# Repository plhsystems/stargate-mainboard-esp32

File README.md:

# Stargate Mainboard ESP32

A fully functional Stargate replica controller based on ESP32, designed to replace Raspberry Pi-based solutions with a more cost-effective and integrated approach.

## Overview

This project provides a complete embedded system for controlling Stargate props designed by Kristian and the "Build The Stargate" community. The ESP32-based solution offers:

- **Lower Cost**: ESP32 modules are significantly cheaper than Raspberry Pi
- **Better Availability**: No shortage issues
- **Integrated Design**: All drivers, regulators, and control circuitry on a single PCB
- **Simpler Wiring**: Fewer external breakouts required
- **Real-Time Control**: FreeRTOS-based deterministic motor control

## Features

### ✅ Implemented

#### Core Functionality
- ✅ **Web Interface**: Full-featured HTTP server with REST API
- ✅ **WiFi**: Station + SoftAP dual-mode support
- ✅ **OTA Updates**: Over-the-air firmware updates
- ✅ **Configuration Management**: JSON import/export
- ✅ **Multiple Gate Types**: Movie/SG1, Atlantis, Universe support

#### Hardware Control
- ✅ **Ring Motor Control**: Stepper motor with precise positioning
- ✅ **Chevron Control**: 9 chevron LED lighting (configurable for 7)
- ✅ **Servo Control**: Chevron locking mechanism (MCPWM-based)
- ✅ **Wormhole LEDs**: 48 NeoPixel LED effects
- ✅ **Ramp Lighting**: PWM-controlled LED brightness
- ✅ **Audio System**: Integrated amplifier with sound effects

#### Advanced Features
- ✅ **Auto-Homing**: Hall sensor-based ring calibration
- ✅ **Auto-Calibration**: Automatic steps-per-rotation detection
- ✅ **BLE Communication**: Wireless control of smart ring LEDs
- ✅ **Address Book**: Hardcoded and fan gate addresses
- ✅ **Incoming Wormholes**: Support for remote gate dialing
- ✅ **Diagnostic Mode**: Hardware testing and troubleshooting

### 🚧 In Progress

- 🚧 **DHD Board Support**: Integration with STM32-based DHD
- 🚧 **SD Card Support**: External storage for audio assets

**Note**: Pablo Board HAL is not yet ready to work and should not be used.

### 📋 Planned

- 📋 **Subspace Network**: Connection to other fan gates
- 📋 **Mobile App**: Dedicated iOS/Android control
- 📋 **Voice Control**: Smart home integration
- 📋 **Advanced Wormhole Effects**: Blackhole, unstable wormhole

## Quick Start

### Prerequisites

- **Hardware**: ESP32-S3 mainboard (pinky-board or compatible)
- **Software**: ESP-IDF 5.3.1
- **Tools**: Python 3.8+, CMake, Ninja

### Installation

1. **Install ESP-IDF 5.3**:
```bash
mkdir -p ~/esp
cd ~/esp
git clone -b v5.3.1 --recursive https://github.com/espressif/esp-idf.git esp-idf-5.3
cd esp-idf-5.3
./install.sh
```

2. **Clone Repository**:
```bash
git clone https://github.com/user/stargate-mainboard-esp32.git
cd stargate-mainboard-esp32
```

3. **Build and Flash**:
```bash
cd firmware/stargate-fw/pinky-board
. ~/esp/esp-idf-5.3/export.sh
idf.py build
idf.py -p /dev/ttyUSB0 flash monitor
```

### First-Time Setup

1. Power on the ESP32
2. Connect to WiFi network `Stargate-Universe`
3. Navigate to `http://192.168.4.1`
4. Follow the setup wizard
5. Configure WiFi and gate type
6. Run homing sequence

## Architecture

The system consists of multiple firmware components:

- **stargate-fw**: Main controller (ESP32-S3)
  - Gate control state machine
  - Web server and REST API
  - WiFi and BLE management
  - Motor control and sensor reading

- **ring-fw**: Smart ring controller (ESP32)
  - BLE server for receiving commands
  - 48 NeoPixel LED control
  - Animation effects and power management

- **ring-factory**: Factory test firmware
  - Hardware diagnostics
  - Burn-in testing
  - Factory reset capability

For detailed architecture information, see [doc/architecture.md](doc/architecture.md).

## Documentation

Comprehensive documentation is available in the [doc/](doc/) directory:

### Essential Reading
- [📖 Architecture](doc/architecture.md) - System design and components
- [🔌 BLE Protocol](doc/ble-protocol.md) - Ring communication details
- [🌐 API Reference](doc/api-reference.md) - HTTP REST API
- [🏠 Homing Algorithm](doc/homing-algorithm.md) - Ring calibration
- [📞 Dial Algorithm](doc/dial-algorithm.md) - Symbol positioning math

### User Guides
- [🎮 Control Page](doc/control-page.md) - Operating the gate
- [⚙️ Configuration](doc/configuration-page.md) - Settings management
- [🔧 Diagnostic Page](doc/diagnostic-page.md) - Troubleshooting
- [📦 OTA Updates](doc/ota-page.md) - Firmware updates

### Technical Details
- [🌌 Stargate Types](doc/stargate-types.md) - Gate specifications
- [🌀 Wormhole Types](doc/wornhole-types.md) - Visual effects
- [📥 Incoming Wormhole](doc/incoming-wormhole.md) - Receiving dials
- [💾 Partitions](doc/partitions.md) - Flash memory layout

## Hardware

### Pinky Board (Production)

**Specifications**:
- MCU: ESP32-S3-WROOM-1
- Flash: 16 MB
- PSRAM: 8 MB
- WiFi: 802.11 b/g/n
- Bluetooth: BLE 5.0

**Connections**:
```
Stepper Motor:  GPIO 25 (Step), GPIO 33 (Dir), GPIO 26 (Sleep)
Servo Motor:    GPIO 4 (MCPWM)
Hall Sensor:    GPIO 32 (Input)
Wormhole LEDs:  GPIO 27 (WS2812B - 48 LEDs)
Ramp LED:       GPIO 23 (PWM)
Status LED:     GPIO 5
```

### Ring Board

**Specifications**:
- MCU: ESP32-WROOM-32
- Flash: 4 MB
- BLE: Server mode

**Connections**:
```
NeoPixel Ring:  GPIO 13 (48 LEDs in 4 concentric rings)
```

## API Examples

### Dial an Address
```bash
curl -X POST http://stargate.local/api/gate/dial \
  -H "Content-Type: application/json" \
  -d '{
    "address": [27, 7, 15, 32, 12, 30, 1],
    "galaxy": "milky_way"
  }'
```

### Get Status
```bash
curl http://stargate.local/api/system/status
```

### Control Ring LEDs
```bash
curl -X POST http://stargate.local/api/ring/animation \
  -H "Content-Type: application/json" \
  -d '{"animation": "fade_in"}'
```

For complete API documentation, see [doc/api-reference.md](doc/api-reference.md).

## Development

### Project Structure
```
stargate-mainboard-esp32/
├── firmware/
│   ├── stargate-fw/        # Main controller
│   │   ├── main-app/       # Application logic
│   │   └── pinky-board/    # Hardware implementation
│   ├── ring-fw/            # Ring controller
│   └── ring-factory/       # Factory test firmware
├── esp32-components/       # Shared utilities
│   └── misc-formula/       # Math functions
├── sgc-components/         # Stargate-specific
│   └── sgu-ringcomm/       # BLE protocol
└── doc/                    # Documentation
```

### Building Different Targets

**Main Controller**:
```bash
cd firmware/stargate-fw/pinky-board
idf.py build
```

**Ring Firmware**:
```bash
cd firmware/ring-fw
idf.py build
```

**Factory Test**:
```bash
cd firmware/ring-factory
idf.py build
```

### Code Style

- C++ Standard: C++17
- Naming: PascalCase for classes, camelCase for methods
- Indentation: 4 spaces
- Comments: Doxygen format for APIs

## Why ESP32 over Raspberry Pi?

| Feature | ESP32 | Raspberry Pi |
|---------|-------|--------------|
| Cost | ~$5-10 | ~$35-75 |
| Availability | Readily available | Frequent shortages |
| Real-time Control | Yes (FreeRTOS) | Limited (Linux) |
| Power Consumption | ~80mA | ~500mA+ |
| Boot Time | <1 second | 20-40 seconds |
| Integration | Single PCB possible | Requires breakouts |
| GPIO | 34 pins | 28 pins (40-pin header) |
| Reliability | No SD card corruption | SD card wear issues |

## Troubleshooting

### Build Issues

**MCPWM API errors**:
- Ensure ESP-IDF 5.3+ is installed
- Check compatibility notes in [doc/architecture.md](doc/architecture.md)

**BLE compilation errors**:
- Add required NimBLE headers
- Include `#undef min` / `#undef max` after includes

**IRAM overflow**:
- Set `CONFIG_COMPILER_OPTIMIZATION_SIZE=y` in sdkconfig

### Runtime Issues

**Ring won't connect**:
- Verify ring is powered
- Check BLE is enabled
- Check logs: `idf.py monitor`

**Stepper doesn't move**:
- Check sleep pin (GPIO 26) is HIGH
- Verify power supply to stepper driver
- Test with manual step command

**Homing fails**:
- Check hall sensor wiring (GPIO 32)
- Run manual homing via web interface
- Verify sensor triggers when magnet is near

## Contributing

Contributions are welcome! Please:

1. Read the documentation in [doc/](doc/)
2. Follow the code style guidelines
3. Test thoroughly on hardware
4. Submit pull requests with clear descriptions

## Community

- **Forum**: [Build The Stargate Community](https://buildthestargateproject.com/)
- **Discord**: [Stargate Builders](https://discord.gg/stargate)
- **YouTube**: [Kristian's Channel](https://youtube.com/kristian)

## License

See [doc/copyright.md](doc/copyright.md) for licensing information.

## Acknowledgments

- **Kristian**: Original Stargate design and inspiration
- **Build The Stargate Project**: Community support
- **Espressif**: ESP-IDF framework
- **Contributors**: Everyone who helped make this possible

---

**Current Version**: 1.0.0
**ESP-IDF Version**: 5.3.1
**Last Updated**: 2026-01-22

For detailed documentation, visit the [doc/](doc/) directory.

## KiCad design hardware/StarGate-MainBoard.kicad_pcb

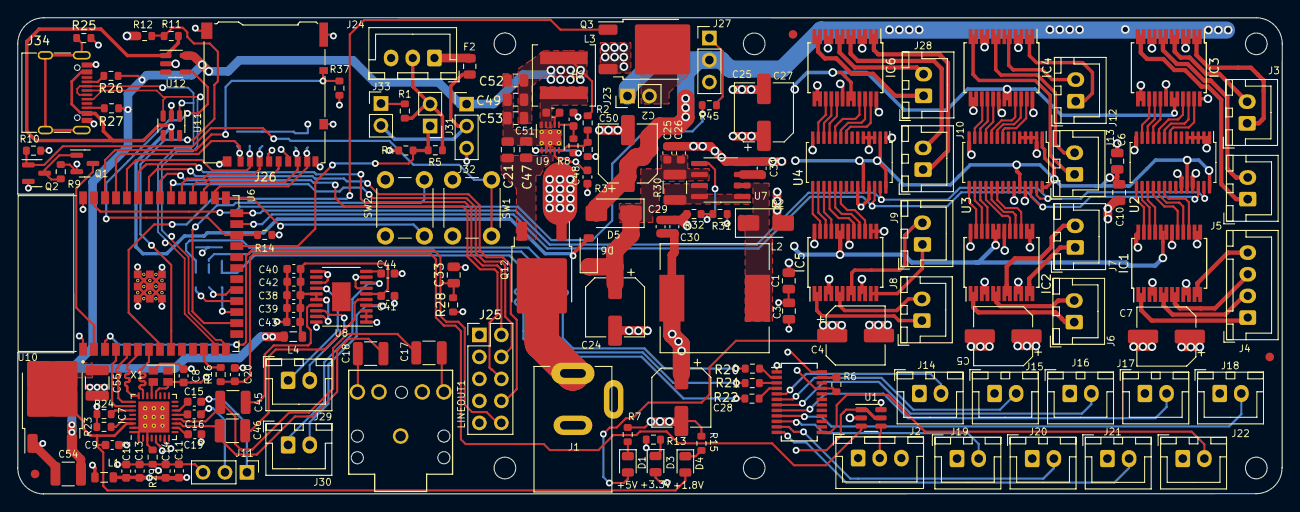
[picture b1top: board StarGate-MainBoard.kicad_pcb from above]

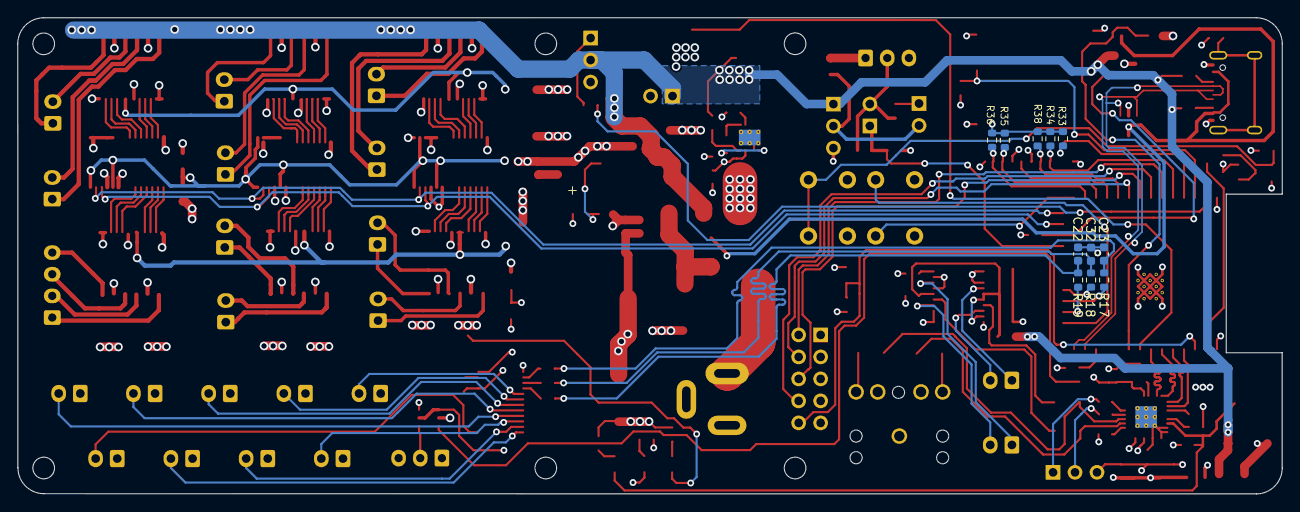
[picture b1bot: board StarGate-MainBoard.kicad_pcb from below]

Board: 4 copper layers, 146.1 x 55.0 mm, 171 parts (11 on the bottom side), 163 nets.

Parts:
C1, C3, C33: 0.1uF; C_0805_2012Metric
C2, C4, C5, C7: 47uF/16V; CP_Elec_6.3x7.7
C6, C10: 10uF; C_0805_2012Metric
C8, C9, C11, C13, C19, C25, C29, C38, C40, C44: 100nF; C_0603_1608Metric
C12, C20, C22, C23, C26, C30, C32, C39, C41: 10nF; C_0603_1608Metric
C14: 4u7F; C_0603_1608Metric
C15, C16, C42, C43: 1uF; C_0603_1608Metric
C17, C18, C45, C46: 100uF 10V; C_1210_3225Metric
C21, C47: 10uF 25V; C_0805_2012Metric
C24: 100uF; CP_Elec_6.3x7.7
C27, C28: 220uF; CP_Elec_6.3x7.7
C31: 120pF; C_0603_1608Metric
C48, C50: 0.1uF; C_0603_1608Metric
C49, C52, C53: 22uF 25V; C_0805_2012Metric
C51: 0.1uF 50V; C_0603_1608Metric
C54: 10uF; C_1210_3225Metric
C55: 22uF; C_1210_3225Metric
D1, D3, D4: LED; LED_0805_2012Metric
D2: STPS2150A; D_SMA
D5: D; D_SMA
D6: D; D_SOD-123
F2: Polyfuse; Fuse_0805_2012Metric
FID1, FID2, FID3: FIDUCIAL""; Fiducial_1mm_Mask2mm
H1, H2, H3, H4, H5, H6: MountingHole; MountingHole_2.5mm
IC1, IC2, IC3, IC4, IC5, IC6: TB6612FNG; SSOP-24_5.3x8.2mm_P0.65mm
IC7: SGTL5000; QFN-32-1EP_5x5mm_P0.5mm_EP3.6x3.6mm_ThermalVias
J1: PJ-037A; CUI_PJ-037A
J2, J24: Conn_01x03_Socket; JST_XH_B3B-XH-A_1x03_P2.50mm_Vertical
J3, J5, J6, J7, J8, J9, J10, J12, J13, J14, J15, J16, J17, J18, J19, J20, J21, J22, J28, J29, J30: Conn_01x02_Pin; JST_XH_B2B-XH-A_1x02_P2.50mm_Vertical
J4: Conn_01x04_Pin; JST_XH_B4B-XH-A_1x04_P2.50mm_Vertical
J11, J27, J32: Conn_01x03_Male; PinHeader_1x03_P2.54mm_Vertical
J23, J31, J33: Conn_01x02_Pin; PinHeader_1x02_P2.54mm_Vertical
J25: Conn_02x05_Odd_Even; PinHeader_2x05_P2.54mm_Vertical
J26: Micro_SD_Card_Det; microSD_HC_Hirose_DM3AT-SF-PEJM5
J34: USB_C_Receptacle; USB_C_Receptacle_G-Switch_GT-USB-7010ASV
L1, L4: 15uH; L_0805_2012Metric
L2: 220uH; L_12x12mm_H4.5mm
L3: 2.2uH 6x6; L_Coilcraft_XAL6060-XXX
LINEOUT1: Phonejack_Stereo_SW; StereoJack_3.5mm_Switch_Cliff_JY039-5P_Horizontal
Q1: FDN340P; SOT-23
Q2: FDN337N; SOT-23
Q3: N0400P-ZK-E1-AY; TO-252-3_TabPin2
Q12: PMOS; TO-252-3_TabPin2
R1, R5: 6.8k; R_0603_1608Metric
R2, R14, R33, R34, R35, R36, R37, R38: 22k; R_0603_1608Metric
R3: 3k; R_0603_1608Metric
R4: 13k; R_0603_1608Metric
R6: R; R_0603_1608Metric
R7, R13, R15: 1K; R_0603_1608Metric
R8: 100k; R_0603_1608Metric
R9, R10, R16, R17, R18, R19, R28: 10k; R_0603_1608Metric
R11: 348k; R_0603_1608Metric
R12: 649k; R_0603_1608Metric
R20, R21, R22: 120R; R_0603_1608Metric
R23, R24: 2k2; R_0603_1608Metric
R25: 1M; R_0603_1608Metric
R26, R27: 5.1k; R_0603_1608Metric
R29: 0R; R_0603_1608Metric
R30: 0R33; R_1210_3225Metric
R31: 6k2; R_0603_1608Metric
R32: 3k9; R_0603_1608Metric
R45: 1k; R_0603_1608Metric
SW1, SW2: SW_Push_Dual; SW_PUSH_6mm
U1: SN74LVC1T45DBV; SOT-23-6
U2, U3, U4: PCA9685; TSSOP-28_4.4x9.7mm_P0.65mm
U5: FM6124; SSOP-24_3.9x8.7mm_P0.635mm
U6: ESP32-S3-WROOM-1-N16R2; XCVR_ESP32-S3-WROOM-1-N16R2
U7: MC33063ADR; SOIC-8_3.9x4.9mm_P1.27mm
U8: TPA6017A2; TSSOP-20-1EP_4.4x6.5mm_P0.65mm_EP2.15x3.35mm
U9: RT6219; WDFN-10-1EP_3x3mm_P0.5mm_EP1.8x2.5mm_ThermalVias
U10: AZ1084-1.8; TO-252-2
U11: USBLC6-4SC6; SOT-23-6
U12: STMPS2151STR; SOT-23-5
X1: SG-210SDF (11.2896MHz); Oscillator_SMD_SeikoEpson_SG210-4Pin_2.5x2.0mm

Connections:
+1V8: C9.1, C55.2, D4.2 (A), IC7.30 (VDDD), U10.2 (VO)
+3.3VA: C11.1, C12.2, C13.2, C14.2, IC7.5 (VDDA), L1.2
+3V3: C1.1, C3.1, C6.1, C8.1, C10.1, C27.1, C28.1, C29.1, C30.1, C48.2, D3.2 (A), IC1.19 (STBY), IC1.20 (VCC), IC2.19 (STBY), IC2.20 (VCC), IC3.19 (STBY), IC3.20 (VCC), IC4.19 (STBY), IC4.20 (VCC), IC5.19 (STBY), IC5.20 (VCC), IC6.19 (STBY), IC6.20 (VCC), IC7.20 (VDDIO), J25.1, J26.4 (VDD), J32.3, L1.1, L2.1, Q1.2 (S), R9.1, R10.1, R23.1, R24.1, R28.1, R31.1, R33.1, R34.1, R35.1, R36.1, R37.1, R38.1, U1.1 (VCCA), U1.5 (DIR), U2.24 (A5), U2.28 (VDD), U3.1 (A0), U3.24 (A5), U3.28 (VDD), U4.2 (A1), U4.24 (A5), U4.28 (VDD), U5.24 (VDD), U9.4 (EN), X1.4 (Vcc)
+5V: C2.1, C4.1, C5.1, C7.1, C49.2, C52.2, C53.2, C54.2, D1.2 (A), D5.2 (A), IC1.13 (VM2), IC1.14 (VM3), IC1.24 (VM1), IC2.13 (VM2), IC2.14 (VM3), IC2.24 (VM1), IC3.13 (VM2), IC3.14 (VM3), IC3.24 (VM1), IC4.13 (VM2), IC4.14 (VM3), IC4.24 (VM1), IC5.13 (VM2), IC5.14 (VM3), IC5.24 (VM1), IC6.13 (VM2), IC6.14 (VM3), IC6.24 (VM1), J2.1, J14.1, J15.1, J16.1, J17.1, J18.1, J19.1, J20.1, J21.1, J22.1, J23.1, J27.2, J32.1, L3.2, L4.2, R2.1, R26.1, R27.1, U1.6 (VCCB), U10.3 (VI), U12.5 (IN)
+12V: C21.2, C47.2, Q12.3 (S), U9.3 (VIN)
/AMP_VDD: C38.1, C39.1, C40.1, C41.1, C42.1, C43.1, L4.1, U8.6 (PVDD), U8.15 (PVDD), U8.16 (VDD), U8.19 (SHUTDOWN)
/BOOT_MODE_A: SW2.2, U6.27 (IO0)
/BOOT_MODE_B: SW2.4, U6.16 (IO46)
/D_N: J34.A7 (D-), J34.B7 (D-), U6.13 (IO19), U11.1 (I/O1)
/D_P: J34.A6 (D+), J34.B6 (D+), U6.14 (IO20), U11.3 (I/O2)
/I2C_SCL_B: IC7.29 (CTRL_CLK), R23.2
/I2C_SDA_B: IC7.27 (CTRL_DATA), R24.2
/I2S_DIN: IC7.26 (I2S_DIN), U6.4 (IO4)
/I2S_DOUT: IC7.25 (I2S_DOUT), U6.5 (IO5)
/I2S_LRCLK: IC7.23 (I2S_LRCLK), U6.7 (IO7)
/I2S_SCLK: IC7.24 (I2S_SCLK), U6.6 (IO6)
/LED1: J14.2, U5.5 (OUT0)
/LED2: J15.2, U5.6 (OUT1)
/LED3: J16.2, U5.7 (OUT2)
/LED4: J17.2, U5.8 (OUT3)
/LED5: J18.2, U5.9 (OUT4)
/LED6: J19.2, U5.10 (OUT5)
/LED7: J20.2, U5.11 (OUT6)
/LED8: J21.2, U5.12 (OUT7)
/LED9: J22.2, U5.13 (OUT8)
/LED_CLK: C32.1, R18.1, R21.1
/LED_LE: C22.1, R19.1, R22.1
/LED_MOSI: C23.1, R17.1, R20.1
/LED_PWM: Q3.2 (G), U6.8 (IO15)
/MTCK: J25.4, U6.32 (IO39)
/MTDI: J25.8, U6.34 (IO41)
/MTDO: J25.6, U6.33 (IO40)
/MTMS: J25.2, U6.35 (IO42)
/NEO_MOSI: C20.1, R16.1, U1.3 (A)
/PROX_IP: J31.1, R4.1, R5.2, U6.23 (IO21)
/PWM1_2: IC3.23 (PWMA), U2.8 (PWM2)
/PWM1_3: IC3.22 (AIN2), U2.9 (PWM3)
/PWM1_4: IC3.21 (AIN1), U2.10 (PWM4)
/PWM1_5: IC3.17 (BIN1), U2.11 (PWM5)
/PWM1_6: IC3.16 (BIN2), U2.12 (PWM6)
/PWM1_7: IC3.15 (PWMB), U2.13 (PWM7)
/PWM1_8: IC1.23 (PWMA), U2.15 (PWM8)
/PWM1_9: IC1.22 (AIN2), U2.16 (PWM9)
/PWM1_10: IC1.21 (AIN1), U2.17 (PWM10)
/PWM1_11: IC1.17 (BIN1), U2.18 (PWM11)
/PWM1_12: IC1.16 (BIN2), U2.19 (PWM12)
/PWM1_13: IC1.15 (PWMB), U2.20 (PWM13)
/PWM2_2: IC4.23 (PWMA), U3.8 (PWM2)
/PWM2_3: IC4.22 (AIN2), U3.9 (PWM3)
/PWM2_4: IC4.21 (AIN1), U3.10 (PWM4)
/PWM2_5: IC4.17 (BIN1), U3.11 (PWM5)
/PWM2_6: IC4.16 (BIN2), U3.12 (PWM6)
/PWM2_7: IC4.15 (PWMB), U3.13 (PWM7)
/PWM2_8: IC2.23 (PWMA), U3.15 (PWM8)
/PWM2_9: IC2.22 (AIN2), U3.16 (PWM9)
/PWM2_10: IC2.21 (AIN1), U3.17 (PWM10)
/PWM2_11: IC2.17 (BIN1), U3.18 (PWM11)
/PWM2_12: IC2.16 (BIN2), U3.19 (PWM12)
/PWM2_13: IC2.15 (PWMB), U3.20 (PWM13)
/PWM3_2: IC6.23 (PWMA), U4.8 (PWM2)
/PWM3_3: IC6.22 (AIN2), U4.9 (PWM3)
/PWM3_4: IC6.21 (AIN1), U4.10 (PWM4)
/PWM3_5: IC6.17 (BIN1), U4.11 (PWM5)
/PWM3_6: IC6.16 (BIN2), U4.12 (PWM6)
/PWM3_7: IC6.15 (PWMB), U4.13 (PWM7)
/PWM3_8: IC5.23 (PWMA), U4.15 (PWM8)
/PWM3_9: IC5.22 (AIN2), U4.16 (PWM9)
/PWM3_10: IC5.21 (AIN1), U4.17 (PWM10)
/PWM3_11: IC5.17 (BIN1), U4.18 (PWM11)
/PWM3_12: IC5.16 (BIN2), U4.19 (PWM12)
/PWM3_13: IC5.15 (PWMB), U4.20 (PWM13)
/SCL: U2.26 (SCL), U3.26 (SCL), U4.26 (SCL), U6.25 (IO48)
/SDA: U2.27 (SDA), U3.27 (SDA), U4.27 (SDA), U6.26 (IO45)
/SD_CK: J26.5 (CLK), U6.30 (IO37)
/SD_CMD: J26.3 (CMD), R38.2, U6.31 (IO38)
/SD_D0: J26.7 (DAT0), R35.2, U6.29 (IO36)
/SD_D1: J26.8 (DAT1), R36.2, U6.28 (IO35)
/SD_D2: J26.1 (DAT2), R33.2, U6.37 (TXD0)
/SD_D3: J26.2 (DAT3/CD), R34.2, U6.36 (RXD0)
/SD_DETECT: J26.10 (DET_A), R37.2, U6.38 (IO2)
/SERVO: R45.1, U6.39 (IO1)
/USB_VBUS_DET: R11.2, R12.1, U6.9 (IO16)
/USB_VBUS_EN: R14.1, U6.24 (IO47), U12.4 (EN)
/VBUS: D6.2 (A), J34.A4 (VBUS), J34.A9 (VBUS), J34.B4 (VBUS), J34.B9 (VBUS), R11.1, U11.5 (VBUS), U12.1 (OUT)
/nRESET: C33.1, J25.10, R28.2, U6.3 (EN)
GND: C1.2, C2.2, C3.2, C4.2, C5.2, C6.2, C7.2, C8.2, C9.2, C10.2, C20.2, C21.1, C22.2, C23.2, C24.2, C25.2, C26.2, C27.2, C28.2, C29.2, C30.2, C31.2, C32.2, C33.2, C47.1, C48.1, C49.1, C50.2, C52.1, C53.1, C54.1, C55.1, D2.2 (A), IC1.3 (PGND1), IC1.4 (PGND1'), IC1.9 (PGND2), IC1.10 (PGND2'), IC1.18 (GND), IC2.3 (PGND1), IC2.4 (PGND1'), IC2.9 (PGND2), IC2.10 (PGND2'), IC2.18 (GND), IC3.3 (PGND1), IC3.4 (PGND1'), IC3.9 (PGND2), IC3.10 (PGND2'), IC3.18 (GND), IC4.3 (PGND1), IC4.4 (PGND1'), IC4.9 (PGND2), IC4.10 (PGND2'), IC4.18 (GND), IC5.3 (PGND1), IC5.4 (PGND1'), IC5.9 (PGND2), IC5.10 (PGND2'), IC5.18 (GND), IC6.3 (PGND1), IC6.4 (PGND1'), IC6.9 (PGND2), IC6.10 (PGND2'), IC6.18 (GND), IC7.1 (GND), IC7.3 (GND), IC7.31 (CTRL_ADR0_CS), IC7.32 (CTRL_MODE), IC7.33 (GND), J1.-\ (2), J2.3, J24.3, J25.3, J25.5, J25.9, J26.6 (VSS), J26.9 (DET_B), J26.11 (SHIELD), J27.3, J34.A1 (GND), J34.A12 (GND), J34.B1 (GND), J34.B12 (GND), Q2.2 (S), Q3.3 (S), Q12.2 (G), R3.2, R4.2, R6.2, R7.1, R12.2, R13.1, R14.2, R15.1, R25.2, R29.2, R32.2, SW1.1, SW1.3, SW2.1, SW2.3, U1.2 (GND), U2.1 (A0), U2.2 (A1), U2.3 (A2), U2.4 (A3), U2.5 (A4), U2.14 (GND), U2.23 (#OE), U2.25 (EXTCLK), U3.2 (A1), U3.3 (A2), U3.4 (A3), U3.5 (A4), U3.14 (GND), U3.23 (#OE), U3.25 (EXTCLK), U4.1 (A0), U4.3 (A2), U4.4 (A3), U4.5 (A4), U4.14 (GND), U4.23 (#OE), U4.25 (EXTCLK), U5.1 (GND), U5.21 (OE), U6.1 (GND), U6.40 (GND), U6.41_1 (GND), U6.41_2 (GND), U6.41_3 (GND), U6.41_4 (GND), U6.41_5 (GND), U6.41_6 (GND), U6.41_7 (GND), U6.41_8 (GND), U6.41_9 (GND), U7.4 (GND), U9.2 (VBYP), U9.11 (PGND), U10.1 (GND), U11.2 (GND), U12.2 (GND), X1.2 (GND)
GNDA: C11.2, C12.1, C13.1, C14.1, C19.2, C38.2, C39.2, C40.2, C41.2, C42.2, C43.2, C44.2, IC7.7 (AGND), J11.3, LINEOUT1.1, R29.1, U8.1 (GND), U8.2 (GAIN0), U8.3 (GAIN1), U8.7 (RIN+), U8.9 (LIN+), U8.11 (GND), U8.13 (GND), U8.20 (GND)
unnamed: C17.2, LINEOUT1.2
unnamed: C18.2, LINEOUT1.4
unnamed: C51.1, L3.1, U9.8 (SW), U9.9 (SW), U9.10 (SW)
unnamed: D1.1 (K), R7.2
unnamed: D2.1 (K), L2.2, U7.2 (SwE)
unnamed: D3.1 (K), R13.2
unnamed: D4.1 (K), R15.2
unnamed: C24.1, C25.1, C26.1, D5.1 (K), D6.1 (K), R30.2, U7.6 (Vin)
unnamed: IC1.1 (AO1), IC1.2 (AO1'), J4.1
unnamed: IC1.5 (AO2), IC1.6 (AO2'), J4.2
unnamed: IC1.11 (BO1), IC1.12 (BO1'), J4.4
unnamed: IC1.7 (BO2), IC1.8 (BO2'), J4.3
unnamed: IC2.1 (AO1), IC2.2 (AO1'), J6.1
unnamed: IC2.5 (AO2), IC2.6 (AO2'), J6.2
unnamed: IC2.11 (BO1), IC2.12 (BO1'), J7.1
unnamed: IC2.7 (BO2), IC2.8 (BO2'), J7.2
unnamed: IC3.1 (AO1), IC3.2 (AO1'), J3.1
unnamed: IC3.5 (AO2), IC3.6 (AO2'), J3.2
unnamed: IC3.11 (BO1), IC3.12 (BO1'), J5.1
unnamed: IC3.7 (BO2), IC3.8 (BO2'), J5.2
unnamed: IC4.1 (AO1), IC4.2 (AO1'), J12.1
unnamed: IC4.5 (AO2), IC4.6 (AO2'), J12.2
unnamed: IC4.11 (BO1), IC4.12 (BO1'), J13.1
unnamed: IC4.7 (BO2), IC4.8 (BO2'), J13.2
unnamed: IC5.1 (AO1), IC5.2 (AO1'), J8.1
unnamed: IC5.5 (AO2), IC5.6 (AO2'), J8.2
unnamed: IC5.11 (BO1), IC5.12 (BO1'), J9.1
unnamed: IC5.7 (BO2), IC5.8 (BO2'), J9.2
unnamed: IC6.1 (AO1), IC6.2 (AO1'), J10.1
unnamed: IC6.5 (AO2), IC6.6 (AO2'), J10.2
unnamed: IC6.11 (BO1), IC6.12 (BO1'), J28.1
unnamed: IC6.7 (BO2), IC6.8 (BO2'), J28.2
unnamed: C15.1, IC7.14 (LINEIN_L)
unnamed: C16.1, IC7.13 (LINEIN_R)
unnamed: C17.1, C45.1, IC7.12 (LINOUT_L)
unnamed: C18.1, C46.1, IC7.11 (LINOUT_R)
unnamed: IC7.21 (SYS_MCLK), X1.3 (OUT)
unnamed: C19.1, IC7.10 (VAG)
unnamed: J1.+\ (1), Q12.1 (D)
unnamed: J2.2, U1.4 (B)
unnamed: C15.2, J11.1
unnamed: C16.2, J11.2
unnamed: J23.2, Q3.1 (D)
unnamed: F2.1, J24.1
unnamed: J24.2, J31.2, R1.1, R5.1
unnamed: J27.1, R45.2
unnamed: J29.1, U8.14 (ROUT-)
unnamed: J29.2, U8.18 (ROUT+)
unnamed: J30.1, U8.8 (LOUT-)
unnamed: J30.2, U8.4 (LOUT+)
unnamed: F2.2, J32.2, J33.2
unnamed: J33.1, R1.2
unnamed: J34.A5 (CC1), R26.2
unnamed: J34.B5 (CC2), R27.2
unnamed: J34.S1 (SHIELD), R25.1
unnamed: Q1.3 (D), U6.2 (3V3)
unnamed: Q1.1 (G), Q2.3 (D), R9.2
unnamed: Q2.1 (G), R10.2, SW1.2, SW1.4
unnamed: R21.2, U5.3 (CLK)
unnamed: R22.2, U5.4 (LE)
unnamed: R6.1, U5.23 (REXT)
unnamed: R20.2, U5.2 (SDI)
unnamed: R16.2, U6.12 (IO8)
unnamed: R19.2, U6.17 (IO9)
unnamed: R17.2, U6.18 (IO10)
unnamed: R18.2, U6.19 (IO11)
unnamed: R30.1, U7.1 (SwC), U7.7 (Ipk), U7.8 (DC)
unnamed: C31.1, U7.3 (TC)
unnamed: R31.2, R32.1, U7.5 (Vfb)
unnamed: C44.1, U8.10 (BYPASS)
unnamed: C46.2, U8.5 (LIN-)
unnamed: C45.2, U8.17 (RIN-)
unnamed: C51.2, U9.7 (BOOT)
unnamed: R2.2, R3.1, U9.5 (FB)
unnamed: R8.2, U9.1 (PGOOD)
unnamed: C50.1, R8.1, U9.6 (VCC)

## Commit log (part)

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2023-12-27 Create hardware folder
2023-12-27 Added JTAG Port
2023-12-28 Added CAP to reset line
2024-01-04 Update readme.md
    More objectives
2024-01-04 Update readme.md
    more clear about the ota
2024-01-04 Create stargate-type.md
    Summary description of each gates
2024-01-04 Update readme.md
    More objectives details
2024-01-04 Update and rename stargate-type.md to stargate-types.md
    Some details and fix spelling
2024-01-04 Create webpage.md
    WebPage structure
2024-01-04 Create wornhole-types.md
    Describe possible wormhole effects.
2024-01-04 Update webpage.md
    Add the wizard page description
2024-01-04 Create wizard.md
    First wizard step.
2024-01-04 Update wizard.md
    Wizard test procedure
2024-01-04 Update wizard.md
    Spelling mistakes
2024-01-04 Update wizard.md
    Ramp output
2024-01-04 Update wizard.md
    Add a todo
2024-01-04 Update misc.md
    Use the math formater
2024-01-04 Update misc.md
    Use math function and table to make the formula readable
2024-01-04 Create diagnostic-page.md
    List possibles errors
2024-01-04 Rename page-wizard.md to wizard-page.md
    rename
2024-01-05 Update webpage.md
    I may decide to fuse the configuration page with Wizard.
2024-01-05 Create configuration-page.md
    Page for configuration
2024-01-05 Update diagnostic-page.md
    System information
2024-01-05 Create control-page.md
    Control page functionality
2024-01-05 Create ota-page.md
    OTA page
2024-01-05 Doc/pinkymaxou/firmware basic doc (#1)
    Basic software documentation.
    * Create readme.md
    * Create stargate-type.md
    * Create webpage.md
    * Create wornhole-types.md
    * Create wizard-page.md
2024-01-05 Update wizard-page.md
    Based the wireguard example on a real config
2024-01-05 Create spin-algorithm.md
    Gate spin algorithm
2024-01-05 Update spin-algorithm.md
    Calculate pos based on the glyph number
2024-01-05 Update spin-algorithm.md
    Calculate the absolute position of a glyph
2024-01-05 Create homing-algorithm.md
    Homing algorithm
2024-01-07 diagram with chevron numbers
2024-01-07 Stargate images
2024-01-10 Gate spinning algorithm
2024-01-10 Doc/pinkymaxou/improve doc (#2)
    * Create partitions.md
    Partitioning
    * Update wizard-page.md
    Based the wireguard example on a real config
    * Create spin-algorithm.md
    Gate spin algorithm
2024-01-12 Basic architecture
2024-01-13 Making a process for the gates
2024-01-13 Add board layer
2024-01-14 Wi-Fi management added
2024-01-14 Remove component
2024-01-14 Feature/pinkymaxou/basic esp32 test (#3)
    * Base project
    * Basic architecture
    * Making a process for the gates
    * Wormhole & Gatecontrol
    * Add board layer
    * Wi-Fi management added
2024-01-14 SNTP
2024-01-14 Working settings
2024-01-14 Template for universe ring (wireless)
2024-01-14 Ring communication
2024-01-14 Ring comm task
2024-01-14 Web interface
2024-01-15 Minimum web server
2024-01-15 Minimum working http server
2024-01-16 Basic API
2024-01-16 Remove useless stuffs
2024-01-16 Feature/pinkymaxou/esp32s3 arch 3 (#5)
    * Web interface
    * Minimum web server
    * At least it start ...
    * Minimum working http server
    * Basic API
    * Add task list
2024-01-16 Add IP addresses to sysinfo
2024-01-17 Add OTA and other APIs
2024-01-17 Move macros
2024-01-17 Update ESP32 component
2024-01-18 Glyph for the milky way
2024-01-18 galaxies symbols
2024-01-18 Rename glyphs
2024-01-18 setup page architecture
2024-01-18 Receive data from stargate project ...
2024-01-18 10 fast attempts for fangate the list
2024-01-18 Feature/pinkymaxou/fangate api (#7)
    * Glyph for the milky way
    * galaxies symbols
    * Glyphs
    * Rename glyphs
    * setup page architecture
    * Receive data from stargate project ...
2024-01-19 List symbols for pegasus and milkyway
2024-01-19 API to get symbols list per galaxy
2024-01-19 Feature/pinkymaxou/addsymbols (#8)
    * Name gate by galaxy instead
    * List symbols for pegasus and milkyway
    * API to get symbols list per galaxy
    * Add API to return symbols
2024-01-19 Hardcoded addresses
2024-01-19 change index type
2024-01-19 Address for the pegasus galaxy
2024-01-19 API to return addresses and symbols
2024-01-20 List of address for each galaxies
2024-01-20 Feature/pinkymaxou/gateaddress book (#9)
    * Hardcoded addresses
    * Universe addresses
    * change index type
    * Address for the pegasus galaxy
    * Changer order
    * API to return addresses and symbols
2024-01-20 Sound FX
2024-01-20 Feature/pinkymaxou/soundfx test (#10)
    * Sound FX
    * Add sound FX assets
    * Sound FX
2024-01-20 CDC example
2024-01-20 HAL for board
2024-01-20 Pinky board
2024-01-21 more information about the abstract HAL
2024-01-21 Feature/pinkymaxou/sequence (#11)
    * HAL for board
    * Rename HAL
    * Pinky board
    * more information about the abstract HAL
    * 1000 hz
2024-01-21 Calibration algorithm
2024-01-21 Working homing but not optimized, full of useless code
2024-01-21 Little bit more streamlined code
2024-01-21 More streamlined auto calibration algorithm
2024-01-21 SGU homing algorithm
2024-01-21 Add ability to cancel the process
2024-01-21 Gate dialing calculations
2024-01-22 Add ramp light animation
2024-01-22 Shortest circle path calculation
2024-01-23 Change stepper acceleration and lowest speed
2024-01-23 Feature/pinkymaxou/dialaddress (#13)
    * Add ability to cancel the process
    * Gate dialing calculations
    * Stepper spin
    * Add ramp light animation
    * Shortest circle path calculation
    * Streamline the stepper function
2024-01-23 Reimporation of the former ring communication component
2024-02-02 test udp
2024-02-03 TCP server test
2024-02-04 the ring communicate and the led pattern is led glitchy
2024-02-05 Ping/Pong
2024-02-07 Bidirectional ring movement + fix wrong ring direction
2024-02-08 dial
2024-02-09 Remove binary
2024-02-09 Remove useless files
2024-02-09 Goto factory even in powering off mode
2024-02-11 Add mutex to HAL, remove useless code
2024-02-11 Some mutex and API to control the ring
2024-02-11 Ring control API fixes
2024-02-12 Galaxy API change
2024-02-12 Gate control argument
2024-02-12 Ability to give argument to commands
2024-02-15 Add dial action with parameters
2024-02-15 Add API access from the page
2024-02-17 Feature/pinkymaxou/refactoring soft (#15)
    * Add mutex to HAL, remove useless code
    * Clean-up
    * Some mutex and API to control the ring
    * Ring control API fixes
    * sound API
    * Galaxy API change
2024-02-17 dial btns
2024-02-17 Test wormhole function
2024-02-17 Not there yet, but it make a nice glitch effect
2024-02-17 Wormhole open/close animation
2024-02-17 Fix always on LEDs
2024-02-18 wormhole
2024-02-18 Feature/pinkymaxou/implement wormhole (#16)
    * dial btns
    * Fix address copy
    * Test wormhole function
    * Not there yet, but it make a nice glitch effect
    * SG1 wormhole running idle
    * Wormhole open/close animation
2024-02-18 Make addresses visible
2024-02-18 Clean-up + activate C++ exceptions
2024-02-19 Return to home even after a cancellation
2024-02-20 Store error and status
2024-02-25 add live status info
2024-03-03 Move to IDF 5.2
2024-03-03 Change font face
2024-03-03 Redirect fan gate data to the API
2024-03-11 fan gate list visible
2024-04-29 Architecture change
2024-04-30 Create ci.yml
    Test automated CI
2024-04-30 Add missing file
2024-04-30 Update ci.yml
    Add submodule
2024-04-30 fix another ...
2024-04-30 fix other file names
2024-04-30 Fix _val
2024-04-30 Another file to fix ...
2024-05-01 New main-app + move stuffs
2024-05-01 Move most of the app into a component
2024-05-01 Ignore useless stuff
2024-05-01 update config
2024-05-01 update ci
2024-05-01 Basic pablo board configuration but doesn't compile yet
2024-05-03 The pinkyboard compile
2024-05-03 Move documents and update the readme.md
2024-05-03 Feature/pinkymaxou/pablo pinout (#23)
    * Basic pablo board configuration but doesn't compile yet
    * The pinkyboard compile
    * Pablo board compiles
    * Move documents and update the readme.md
2024-05-07 Gate type setting
2024-05-08 Move some functions
2024-05-08 Settings page
2024-05-08 Update the wizzard doc
2024-05-08 Feature/pinkymaxou/page settings (#25)
    * Settings page
    * Update the wizard doc
2024-05-24 Move the stepper code into the specific hardware part
2024-05-24 Feature/maxou/move stepper code (#26)
    * Settings page
    * Update the wizzard doc
    * Fix typo
    * log
    * Move the stepper code into the specific hardware part
2024-09-08 Lock and release clamp code
2024-09-08 Fix a bug where the ring comm randomly disconnect. Add a 5s delay after the gate shutdown for effect.
2024-09-10 Attempt to fix delay in ring comm
2024-09-10 Put a 5 minutes delay before closing the gate
2024-09-10 Ring comm still doesn't work well
2024-09-10 formatting mostly
2026-01-20 test
2026-01-26 Use IDF 5.5 + Refactor + Use BLE instead of WiFi+UDP
    fix SDK config
    fix
    attempt to fix the BLE client
    Attempt at dial computer interface
    Improvement
    othe rtest
2026-01-27 Compile on ESP-IDF 5.5
2026-01-27 Fix the CI
2026-01-28 attempt to fix a random crash related to exception
2026-01-28 Fix UUID
2026-01-29 Bugfix/maxou/fix a few crash (#29)
    * attempt to fix a random crash related to exception
    * Fix UUID
    * Seems to fix the RMT bug
2026-01-29 Still crash after some time :|
2026-01-29 Back to 50 HZ
2026-01-31 Add sound effect and fix the wifi crash
2026-01-31 Feature/mcarrier/rmt test 2 (#30)
    * Still crash after some time :|
    * Back to 50 HZ
    * fix priority and rtos speed
    [R] update documentation and pablo board config
    [R] update sdk config
    Refactoring
2026-01-31 [R] update sdk config
2026-01-31 Add errors code
2026-02-01 fix doc
2026-02-01 SG Result
2026-04-02 Feature/architecture improvements (#31)
    * fix priority and rtos speed
    * [R] update sdk config
    * Add architecture improvements: Result types, state machine, task priorities
    - Add Result<T> type for typed error handling (replaces bool returns)
    - Add GateStateMachine for formal state transitions
    - Update FreeRTOS task priorities (GateControl highest, WebServer lowest)
2026-04-10 feat(ui): new SGU-themed control interface
    Complete rewrite of the web control interface with an Ancient/SGU aesthetic:
    - Tabbed layout: Dial, Manual Control, System Info, Network, Settings
    - Glyph ring dial with address book and slot bar
    - Animated vortex gate center (spinning rings, gold glow when dialing)
    - Fan gate network tab with milkyway glyph address display
    - Settings tab with editable parameters and save button
2026-04-10 fix(http): fix fan gate list fetch and heap fragmentation
    - Fix SystemAPI fangate endpoint: bad C-cast of shared_ptr replaced with .get()
    - Fix chunked HTTP read: esp_http_client_get_content_length() returns -1 for
    PHP APIs using chunked transfer encoding; read in 512-byte chunks instead
    - Use a static read buffer (BSS) to avoid repeated 32KB heap alloc/free cycles
    - Only allocate a right-sized buffer for the actual response data
    - Add null check on esp_http_client_init return value
2026-04-10 refactor: apply coding style guide across codebase
    - Allman braces: opening { on its own line throughout
    - Yoda conditions: constant on left of == and !=
    - Remove Hungarian notation (p_, b_, u8_, u32_, sz_, etc.)
    - lowerPascalCase free functions (hwErrorToString, gateStateToString, bleHostTask, etc.)
    - snake_case local variables and parameters
    - Pointer star near type: char* x not char *x
